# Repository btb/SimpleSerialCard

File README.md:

# Simple Serial Card

This is a copy of the board at https://github.com/jmthompson/ssc just with a two-layer PCB and it uses 14(C)88 and 14(C)89 chips instead of a pair of MAX3232s. You also don't need the eight electrolytic caps. Otherwise it works (or doesn't) in the same ways, and suffers the same issues as that board. For a board that is a more direct clone of the Super Serial Card II, see https://github.com/btb/SuperSerial

## Overview

The Simple Serial Card is a low-cost Super Serial Card work-a-like. I designed
this because I needed a way to use ADTPro on my Apple IIe, and the price of
super serial cards on eBay is getting a bit high for my taste.

This card is more or less 100% compatible with the original Apple card. It
uses the same 6551 ACIA mapped to the same I/O locations, and in fact can
use the same firmware ROM.  It does however have some minor differences in the
interest of cost:

1. There are no DIP switches, so you cannot set the default configuration. It
   does, however, include a jumper that can be removed to disable IRQs.
2. Instead of a DB-25 it is wired to use a DB-9 cable like those used by PC
   motherboards.
3. There is no terminal/modem block to change the serial port wiring. Just use
   the appropriate cable instead, or a null modem adapter.

The KiCAD schematics and PCB layout are included. It is a four layer board,
because my fab house of choice charges the same for 2 and 4 layers, so I went
with what made the layout easier.

## Parts List

* A 74HCT245 octal bus transceiver (U1)
* A 28C256 EEPROM (U2)
* A 1.8432 MHz 5V oscillator (U3)
* A 22V10 GAL (any speed or variety should work) (U4)
* A W65C51N ACIA (U5)
* Two MAX3232 RS-232 line transceivers (U6, U7)
* Seven 0.1uf ceramic bypass caps (C1-C7)
* Eight 1uf 16V electrolytic caps (C9-C16)
* A 2x5 pin header (J1)
* A 1x2 pin header (J2)

## Assembly

Before assembly you will need to burn firmware ROM into the EEPROM, and burn
the appropriat equations into the GAL. See "Burning the ROM" and "Burning the
GAL" below for more details.

I would suggest socketing all of the chips, but at the very least socket the
ROM and the GAL in case you need to update them.

As mentioned above the header on this card is wired the same as a PC COM
header. There are two varieties of these cables available; this card uses the
newer style which is wired 1:1; that is, pin 1 on the header goes to pin 1
on the DB-9, pin 2 to pin 2, etc. These are sometimes referred to as
"AT/EVEREX" style cables.

There is an asterisk on the card's silkscreen indicating pin one on the RS-232
header; make sure this lines up with pin one on your ribbon cable. Usually this
is the red wire on the ribbon cable.

## Installation

Turn off the computer, put the card in an empty slot, and mount the DB-9 on one
of the small cutouts on the back of the computer (or just run the ribbon cable
through an open cutout if you don't care).

## Design Considerations

Many parts choices were influenced by what I have already in my parts bin, even
if that makes the design non-optimal. For example, I used MAX3232 line drivers
because I have a ton of them. With 12V available on the slots I could've used
different parts and avoided all the charge pump caps, but I didn't feel like
buying more chips.

With the exception of the 22V10 GAL used for glue logic all parts in this design
are still actively available. The GALs are out of production but still readily
available on eBay or Aliexpress (though YMMV as far as quality).

## Burning the ROM

A standard super serial card image should work fine with this card, though
since there are no configuration switches the default settings after power on
or reset will be somewhat random.  Once I have working cards built I will be
creating a customized firmware ROM that sets the defaults to 9600 bps for the
ADT Pro bootstrap.

Since 2K EPROMs are nearly impossible to find I subbed in an AT28C256 EEPROM
(again, I had one already). Only the lower 2K is used by the card, so when
burning you can either duplicate the image 16 times, or fill the upper 30K
with zeroes or some other random data. In theory a AT28C64 EEPROM should also
work (and only waste 6K), but I don't have one to test, and a brief search
suggests they aren't any cheaper than the AT28C256 (presumably because they
are out of production).

I use the TL866 II+ USB programmer along with the minipro Linux client for my
ROM burns.

## Burning the GAL

The equations for the GAL are included as a .pld file for the GALasm program.
If you run Linux or another OS that can run GNU make then you should be able
to just type "make" in the "gal" subfolder to compile the equations into a
.jed file.  Burning this file requires a suitable programmer; I personally
use the same TL866 II+ that I use for burning ROMs, though at least at the time
of this writing the minipro client doesn't know how to burn GALs properly, so
you'll need to use the official client software, either on a Windows PC or
under Wine.

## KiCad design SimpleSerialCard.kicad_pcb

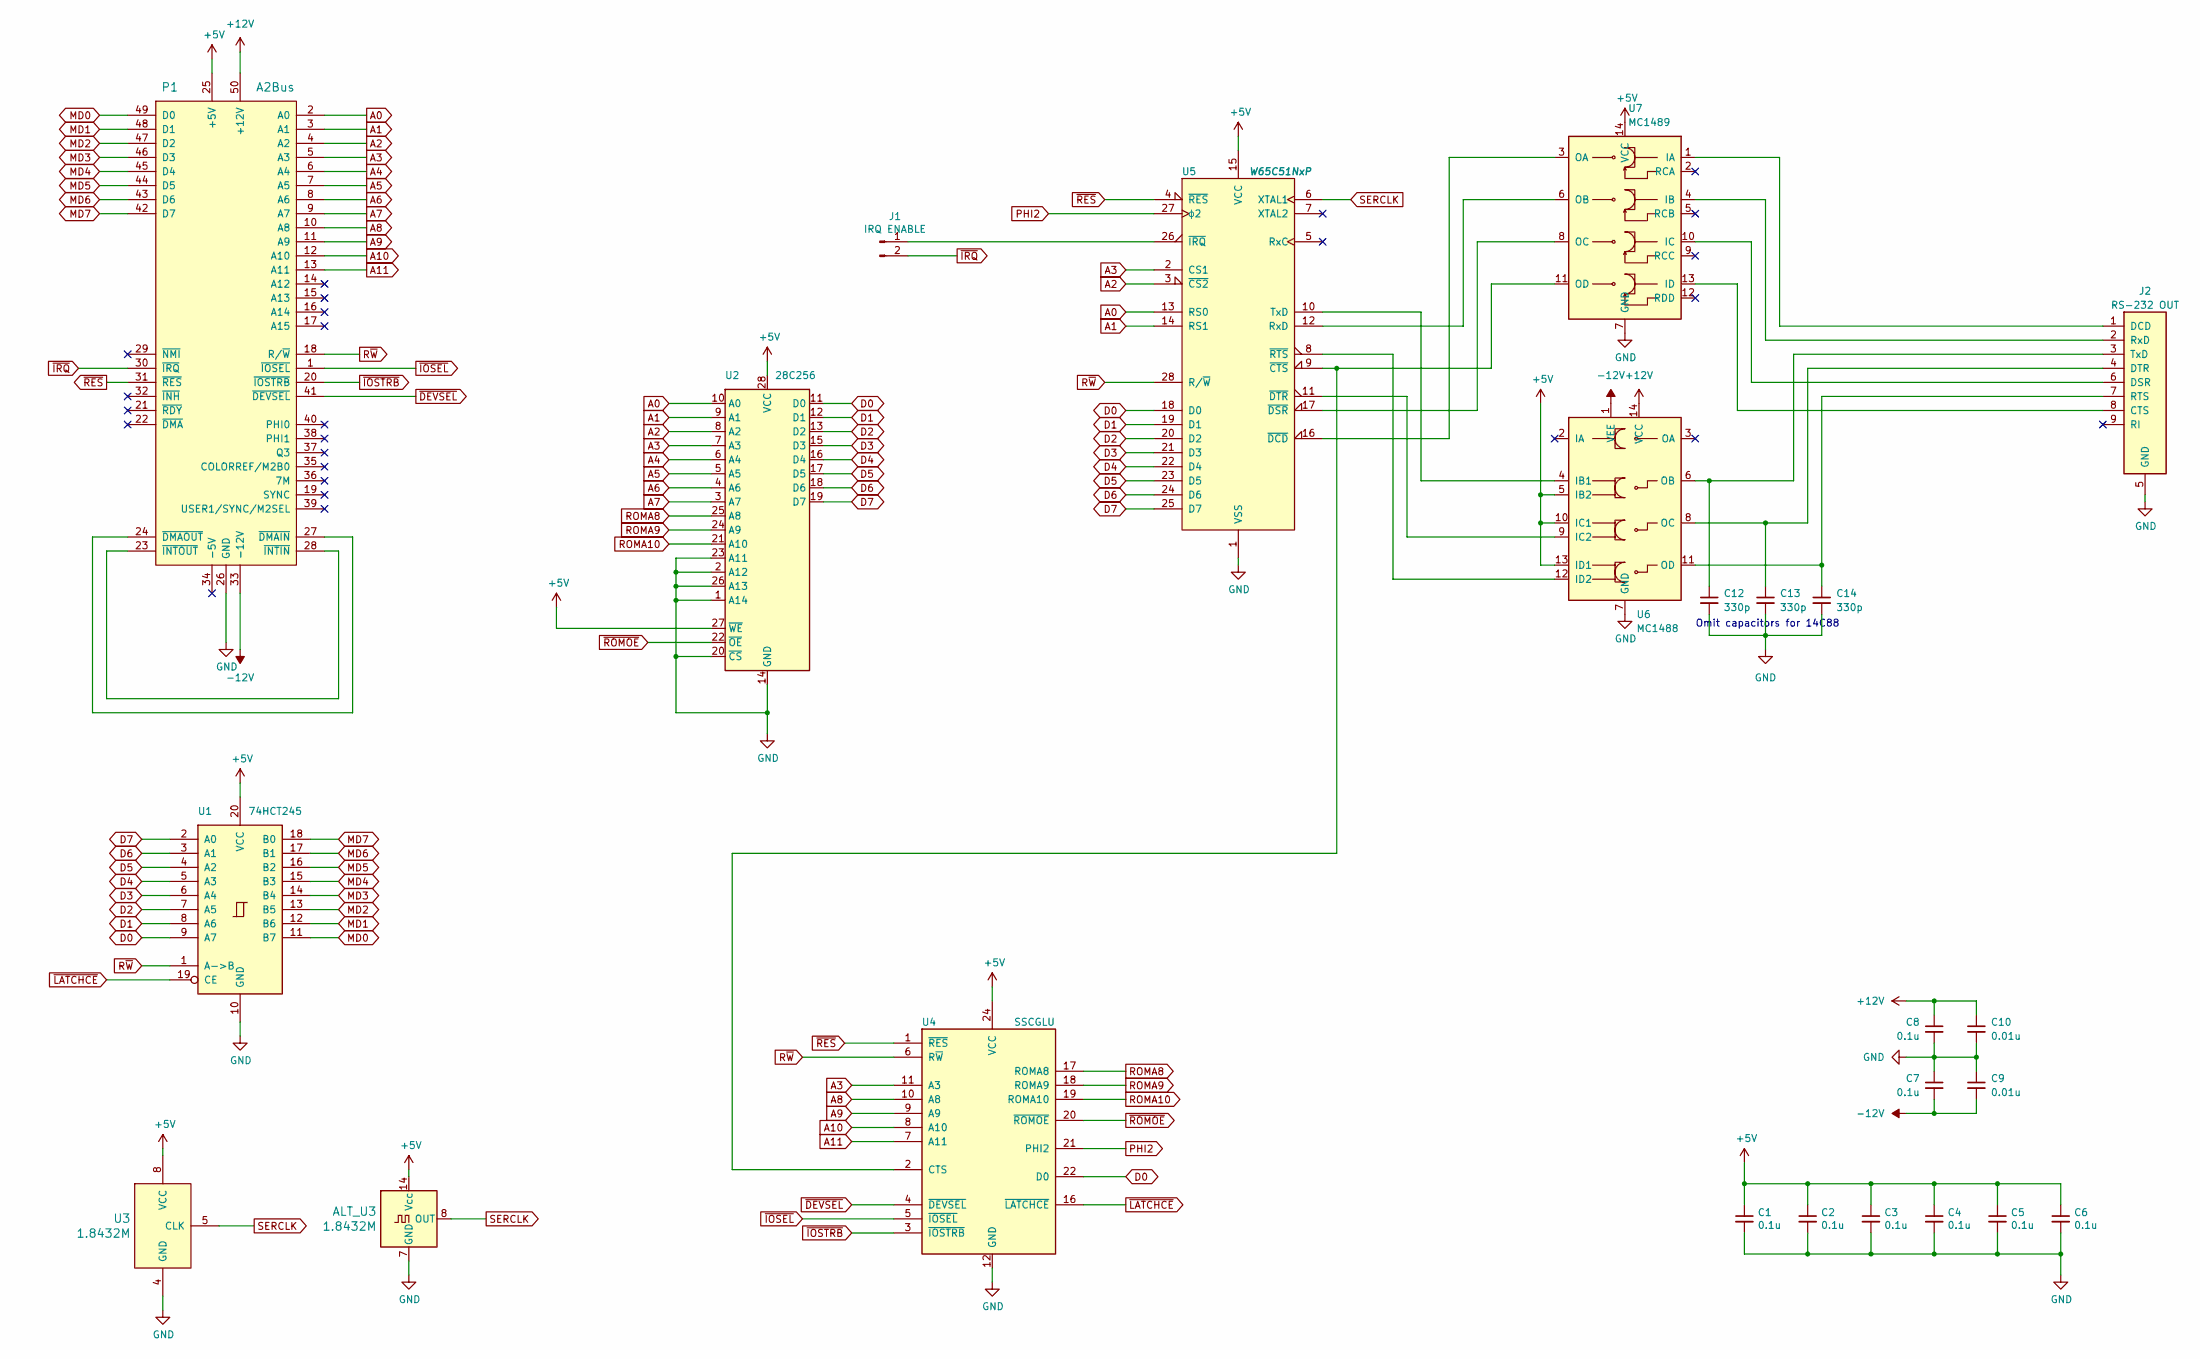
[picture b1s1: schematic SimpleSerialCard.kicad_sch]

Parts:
ALT_U3: 1.8432M; Oscillator_DIP-14
C1, C2, C3, C4, C5, C6, C7, C8: 0.1u; C_Disc_D4.3mm_W1.9mm_P5.00mm
C9, C10: 0.01u; C_Disc_D4.3mm_W1.9mm_P5.00mm
C12, C13, C14: 330p; C_Disc_D3.0mm_W1.6mm_P2.50mm
J1: IRQ ENABLE; PinHeader_1x02_P2.54mm_Vertical
J2: RS-232 OUT; PinHeader_2x05_P2.54mm_Vertical
P1: A2Bus; Male_Card-Edge_50_pin__100_mil
U1: 74HCT245; DIP-20_W7.62mm_Socket
U2: 28C256; DIP-28_W15.24mm_Socket
U3: 1.8432M; DIP-8_W7.62mm_Socket
U4: SSCGLU; DIP-24_W7.62mm_Socket
U5: W65C51NxP; DIP-28_W15.24mm_Socket
U6: MC1488; DIP-14_W7.62mm
U7: MC1489; DIP-14_W7.62mm

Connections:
+5V: ALT_U3.14 (Vcc), C1.1, C2.1, C3.1, C4.1, C5.1, C6.1, P1.25 (+5V), U1.20 (VCC), U2.27 (~WE), U2.28 (VCC), U3.8 (VCC), U4.24 (VCC), U5.15 (VCC), U6.5 (IB2), U6.10 (IC1), U6.13 (ID1), U7.14 (VCC)
+12V: C8.1, C10.1, P1.50 (+12V), U6.14 (VCC)
-12V: C7.2, C9.2, P1.33 (-12V), U6.1 (VEE)
A0: P1.2 (A0), U2.10 (A0), U5.13 (RS0)
A1: P1.3 (A1), U2.9 (A1), U5.14 (RS1)
A2: P1.4 (A2), U2.8 (A2), U5.3 (~CS2)
A3: P1.5 (A3), U2.7 (A3), U4.11 (A3), U5.2 (CS1)
A4: P1.6 (A4), U2.6 (A4)
A5: P1.7 (A5), U2.5 (A5)
A6: P1.8 (A6), U2.4 (A6)
A7: P1.9 (A7), U2.3 (A7)
A8: P1.10 (A8), U4.10 (A8)
A9: P1.11 (A9), U4.9 (A9)
A10: P1.12 (A10), U4.8 (A10)
A11: P1.13 (A11), U4.7 (A11)
D0: U1.9 (A7), U2.11 (D0), U4.22 (D0), U5.18 (D0)
D1: U1.8 (A6), U2.12 (D1), U5.19 (D1)
D2: U1.7 (A5), U2.13 (D2), U5.20 (D2)
D3: U1.6 (A4), U2.15 (D3), U5.21 (D3)
D4: U1.5 (A3), U2.16 (D4), U5.22 (D4)
D5: U1.4 (A2), U2.17 (D5), U5.23 (D5)
D6: U1.3 (A1), U2.18 (D6), U5.24 (D6)
D7: U1.2 (A0), U2.19 (D7), U5.25 (D7)
GND: ALT_U3.7 (GND), C1.2, C2.2, C3.2, C4.2, C5.2, C6.2, C7.1, C8.2, C9.1, C10.2, C12.2, C13.2, C14.2, J2.5 (GND), P1.26 (GND), U1.10 (GND), U2.1 (A14), U2.2 (A12), U2.14 (GND), U2.20 (~CS), U2.23 (A11), U2.26 (A13), U3.4 (GND), U4.12 (GND), U5.1 (VSS), U6.7 (GND), U7.7 (GND)
MD0: P1.49 (D0), U1.11 (B7)
MD1: P1.48 (D1), U1.12 (B6)
MD2: P1.47 (D2), U1.13 (B5)
MD3: P1.46 (D3), U1.14 (B4)
MD4: P1.45 (D4), U1.15 (B3)
MD5: P1.44 (D5), U1.16 (B2)
MD6: P1.43 (D6), U1.17 (B1)
MD7: P1.42 (D7), U1.18 (B0)
unnamed: C12.1, J2.3 (TxD), U6.6 (OB)
unnamed: C13.1, J2.4 (DTR), U6.8 (OC)
unnamed: C14.1, J2.7 (RTS), U6.11 (OD)
unnamed: J1.1, U5.26 (~IRQ)
unnamed: J2.1 (DCD), U7.1 (IA)
unnamed: J2.2 (RxD), U7.4 (IB)
unnamed: J2.6 (DSR), U7.10 (IC)
unnamed: J2.8 (CTS), U7.13 (ID)
unnamed: P1.23 (~INTOUT), P1.28 (~INTIN)
unnamed: P1.24 (~DMAOUT), P1.27 (~DMAIN)
unnamed: U4.2 (CTS), U5.9 (~CTS), U7.11 (OD)
unnamed: U5.8 (~RTS), U6.12 (ID2)
unnamed: U5.10 (TxD), U6.4 (IB1)
unnamed: U5.11 (~DTR), U6.9 (IC2)
unnamed: U5.12 (RxD), U7.6 (OB)
unnamed: U5.16 (~DCD), U7.3 (OA)
unnamed: U5.17 (~DSR), U7.8 (OC)
PHI2: U4.21 (PHI2), U5.27 (ϕ2)
ROMA8: U2.25 (A8), U4.17 (ROMA8)
ROMA9: U2.24 (A9), U4.18 (ROMA9)
ROMA10: U2.21 (A10), U4.19 (ROMA10)
R~W: P1.18 (R/~W), U1.1 (A->B), U4.6 (R~W), U5.28 (R/~W)
SERCLK: ALT_U3.8 (OUT), U3.5 (CLK), U5.6 (XTAL1)
~DEVSEL: P1.41 (~DEVSEL), U4.4 (~DEVSEL)
~IOSEL: P1.1 (~IOSEL), U4.5 (~IOSEL)
~IOSTRB: P1.20 (~IOSTRB), U4.3 (~IOSTRB)
~IRQ: J1.2, P1.30 (~IRQ)
~LATCHCE: U1.19 (CE), U4.16 (~LATCHCE)
~RES: P1.31 (~RES), U4.1 (~RES), U5.4 (~RES)
~ROMOE: U2.22 (~OE), U4.20 (~ROMOE)

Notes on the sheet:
Omit capacitors for 14C88

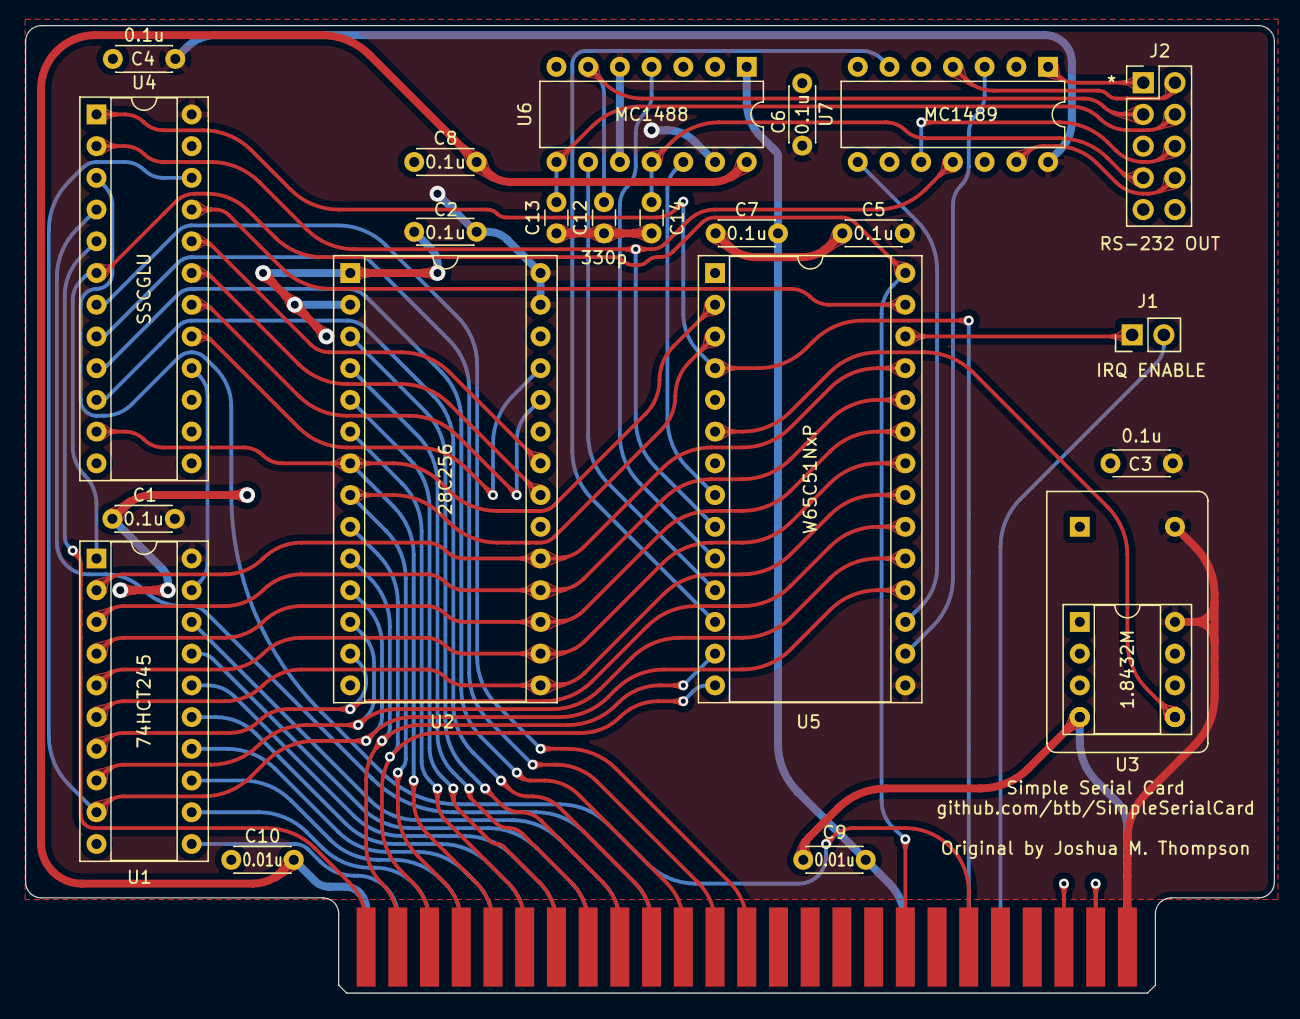
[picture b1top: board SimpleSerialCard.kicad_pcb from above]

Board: 2 copper layers, 100.0 x 77.5 mm, 24 parts (0 on the bottom side), 62 nets.

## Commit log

2022-10-16 Rename, update to kicad 6, use MC1488/89
2022-10-16 remove & ignore fp-info-cache
2022-10-18 reroute everything
2022-10-18 add gerbers
